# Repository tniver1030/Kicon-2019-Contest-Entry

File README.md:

# KiCon 2019 Contest!

This is a modified version of the KiCon 2019 conference badge.

## Rules

https://kicad-kicon.com/contest

## Direct download of files

Use this link: https://github.com/ChrisGammell/KiCon-2019-Contest/archive/master.zip

## Original board files

https://github.com/orsonmmz/kicon19-badge-hw

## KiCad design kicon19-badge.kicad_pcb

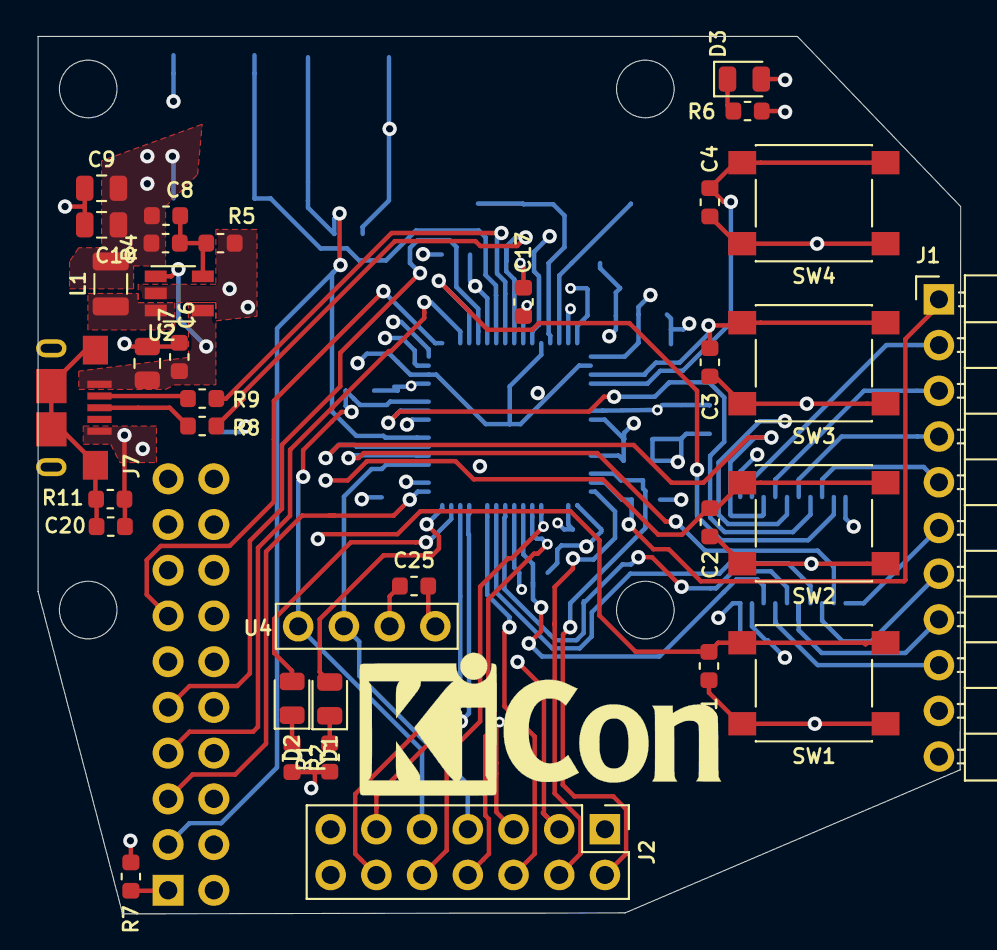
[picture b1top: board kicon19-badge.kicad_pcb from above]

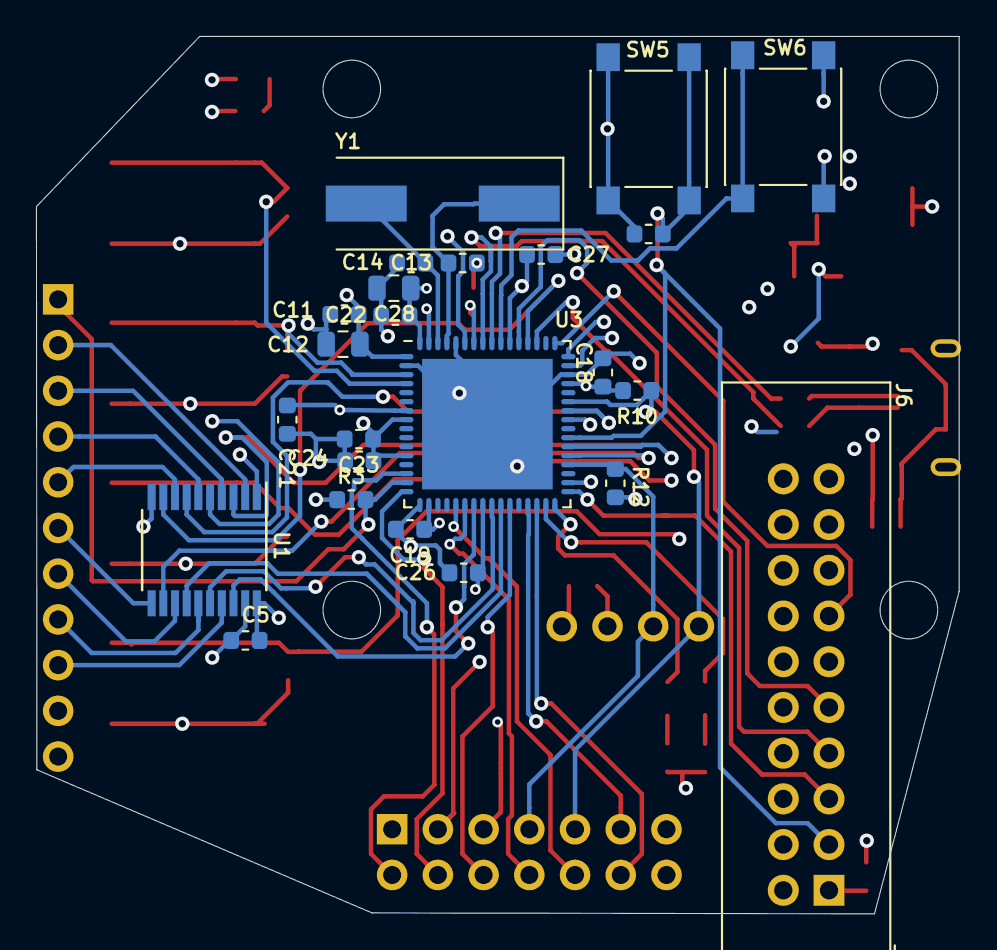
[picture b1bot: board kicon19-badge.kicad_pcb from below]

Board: 4 copper layers, 51.3 x 48.7 mm, 59 parts (25 on the bottom side), 58 nets.

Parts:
C1, C2, C3, C4, C5, C6, C11, C16, C17, C18, C19, C21, C22, C23, C24, C25, C26, C27: 100n; C_0603_1608Metric
C7, C9, C10: 22u/6.3V; C_0805_2012Metric
C8, C13, C14: 22p; C_0603_1608Metric
C12, C28: 4.7u; C_0805_2012Metric
C20: 1n; C_0603_1608Metric
D1, D2, D3: LED; LED_0805_2012Metric
H1: Clip; ClipHole
J1: LogicProbes; PinHeader_1x11_P2.54mm_Horizontal
J2: Ports; PinHeader_2x07_P2.54mm_Vertical
J6: Conn_ARM_JTAG_SWD_20; IDC-Header_2x10_P2.54mm_Vertical
J7: USB_B_Micro; 10118193-0001LF
L1: 2.2u; L_1007_2518Metric
R1, R2, R6: 120; R_0603_1608Metric
R3, R8, R9: 22; R_0603_1608Metric
R4: 300k; R_0603_1608Metric
R5: 68k; R_0603_1608Metric
R7: DNF_22; R_0603_1608Metric
R10, R12: 1k5; R_0603_1608Metric
R11: 1M; R_0603_1608Metric
SW1: BTN1; SW_SPST_PTS645
SW2: BTN2; SW_SPST_PTS645
SW3: BTN3; SW_SPST_PTS645
SW4: BTN4; SW_SPST_PTS645
SW5: Reset; SW_SPST_PTS645
SW6: Erase; SW_SPST_PTS645
U1: 74LCX244MTC; TSSOP-20_4.4x6.5mm_P0.65mm
U2: AP3429A; TSOT-23-5
U3: ATSAM4SD16BA-MU; QFN-64-1EP_9x9mm_P0.5mm_EP7.25x7.25mm
U4: OLED_SSD1306
Y1: 12M; Crystal_SMD_HC49-SD

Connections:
+1V2: C22.1, C23.1, C24.1, C26.1, C27.1, C28.1, U3.8, U3.12, U3.24, U3.54, U3.64
+3V3: C5.2, C8.1, C9.1, C10.1, C11.1, C12.1, C17.1, C18.1, C19.1, C21.1, C25.1, D3.2, J1.11, J2.1, L1.2, R4.2, R7.1, R10.2, R12.2, SW6.1, U1.20, U3.1, U3.7, U3.18, U3.45, U3.58, U4.2
/ADC0: J2.4, U3.16
/ADC1: J2.2, U3.14
/BTN1: C1.2, SW1.2, U3.47
/BTN2: C2.2, SW2.2, U3.48
/BTN3: C3.2, SW3.2, U3.3
/BTN4: C4.2, SW4.2, U3.4
/DAC0: J2.5, U3.59
/DAC1: J2.3, U3.63
/MISO: J2.6, U3.27
/MOSI: J2.8, U3.22
/NRST: C16.2, J6.3, SW5.2, U3.39
/PCK0: R3.1, U3.34
/PIODCCLK: J1.1, R3.2, U3.15
/PROBE0: U1.18, U3.23
/PROBE1: U1.16, U3.25
/PROBE2: U1.14, U3.26
/PROBE3: U1.12, U3.37
/PROBE4: U1.3, U3.38
/PROBE5: U1.5, U3.41
/PROBE6: U1.7, U3.42
/PROBE7: U1.9, U3.52
/PROBE_IN0: J1.2, U1.2
/PROBE_IN1: J1.3, U1.4
/PROBE_IN2: J1.4, U1.6
/PROBE_IN3: J1.5, U1.8
/PROBE_IN4: J1.9, U1.17
/PROBE_IN5: J1.8, U1.15
/PROBE_IN6: J1.7, U1.13
/PROBE_IN7: J1.6, U1.11
/SCK: J2.10, U3.21
/SCL: J2.7, R12.1, U3.36, U4.3
/SDA: J2.9, R10.1, U3.43, U4.4
/TCK: J6.9, U3.53
/TDI: J6.5, U3.33
/TDO: J6.13, U3.49
/TMS: J6.7, U3.51
/UART_RX: J2.12, U3.30
/UART_TX: J2.11, U3.29
/USB1_D+: J7.3, R8.2
/USB1_D-: J7.2, R9.2
/USB_D+: R8.1, U3.57
/USB_D-: R9.1, U3.56
GND: C1.1, C2.1, C3.1, C4.1, C5.1, C6.2, C7.2, C9.2, C10.2, C11.2, C12.2, C13.2, C14.2, C16.1, C17.2, C18.2, C19.2, C20.2, C21.2, C22.2, C23.2, C24.2, C25.2, C26.2, C27.2, C28.2, J1.10, J2.13, J2.14, J6.4, J6.6, J6.8, J6.10, J6.12, J6.14, J6.16, J6.18, J6.20, J7.5, R1.2, R2.2, R5.1, R6.2, R11.1, SW1.1, SW2.1, SW3.1, SW4.1, SW5.1, U1.1, U1.10, U1.19, U2.2, U3.2, U3.17, U3.46, U3.60, U3.65, U4.1
unnamed: C8.2, R4.1, R5.2, U2.5
unnamed: C13.1, U3.61, Y1.1
unnamed: C14.1, U3.62, Y1.2
unnamed: C20.1, J7.6, R11.2
unnamed: D1.1, R1.1
unnamed: D1.2, U3.32
unnamed: D2.1, R2.1
unnamed: D2.2, U3.31
unnamed: D3.1, R6.1
unnamed: J6.1, R7.2
unnamed: L1.1, U2.3
unnamed: SW6.2, U3.55
VBUS: C6.1, C7.1, J7.1, U2.1, U2.4

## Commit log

2019-05-07 Init Commit

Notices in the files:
kicon19-badge.kicad_pcb:
Copyright Maciej Suminski 2019
This documentation describes Open Hardware and is licensed under the CERN OHL v. 1.2.
You may redistribute and modify this documentation under the terms of the
CERN OHL v.1.2. (http://ohwr.org/cernohl). This documentation is distributed
